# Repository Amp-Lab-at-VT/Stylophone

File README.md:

## Members
Jivitesh Kukreja, Electrical Engineering (2024)\
jiviteshkuk26@vt.edu

## Repo Link
<a class="button is-link" href="https://github.com/Amp-Lab-at-VT/Stylophone">Stylophone</a>

## Photo
/web/img/Stylophone/hero.png

## Mentor
Richard Gibbons

## Current Status
In Progress

## Project Overview
# About Stylophone
Stylophone is a musical instrument that contains 20 keys each associated with a distinct musical note. Every time the stylus touches a key frequency associated with that key is heard on the speaker. 
Stylophone can shfit the octace associated with a key, up or down with a flick of a switch. There is also vibrato mode which is basically modulating the frequency of each key to make it sound "alienish".
# About This Project
This Project aims to reverse engineering a stylophone using a modern TLC555 timer IC and a old Programable Unijunction Transistor. 
The resevred engineered version aims to included modern features like power using type C, low power consumtion while idle and under load, support for low impedance speaker, and rechargable battery. 
This project also serves to see which sounds better the digital version based on the 555 timer or the analog version based on PUT as the orginal stylophone.

## Educational Value Added
This Project with help me learn:
1. How to design low frequency oscillators
2. How to a simple audio amplifier 
3. How to design PCB

## Tasks
1. Design a square wave generator using TLC555 that produces different frequencies with different resistor values.
2. Design an audio amplifier that drives the speaker.
3. Design a low-frequency sine wave generator for vibrato effect.
4. Power everything with a USB C connector. 

[//]: #Design Decisions

[//]: ## Design Misc

[//]: ## Steps for Documenting Your Design Process

## Fabrication Files
<a class="button is-link" href="https://github.com/Amp-Lab-at-VT/Stylophone/blob/main/Fabrication%20Files/PUT/gerber_files_with_battery.zip">Gerber Files</a>
<a class="button is-link" href="https://github.com/Amp-Lab-at-VT/Stylophone/blob/main/Fabrication%20Files/PUT/Stylophone_with_battery.csv">Bill Of Materials</a>

## Timeline
SEPTEMBER: Circuit Design\
OCTOBER: PCB Design and Protoboard Testing\
NOVEMBER: Assembly and Testing\

## Useful Links
https://www.waitingforfriday.com/?p=334 \
https://www.instructables.com/Retro-Stylophone-NE555-Based/

[//]: ## Log

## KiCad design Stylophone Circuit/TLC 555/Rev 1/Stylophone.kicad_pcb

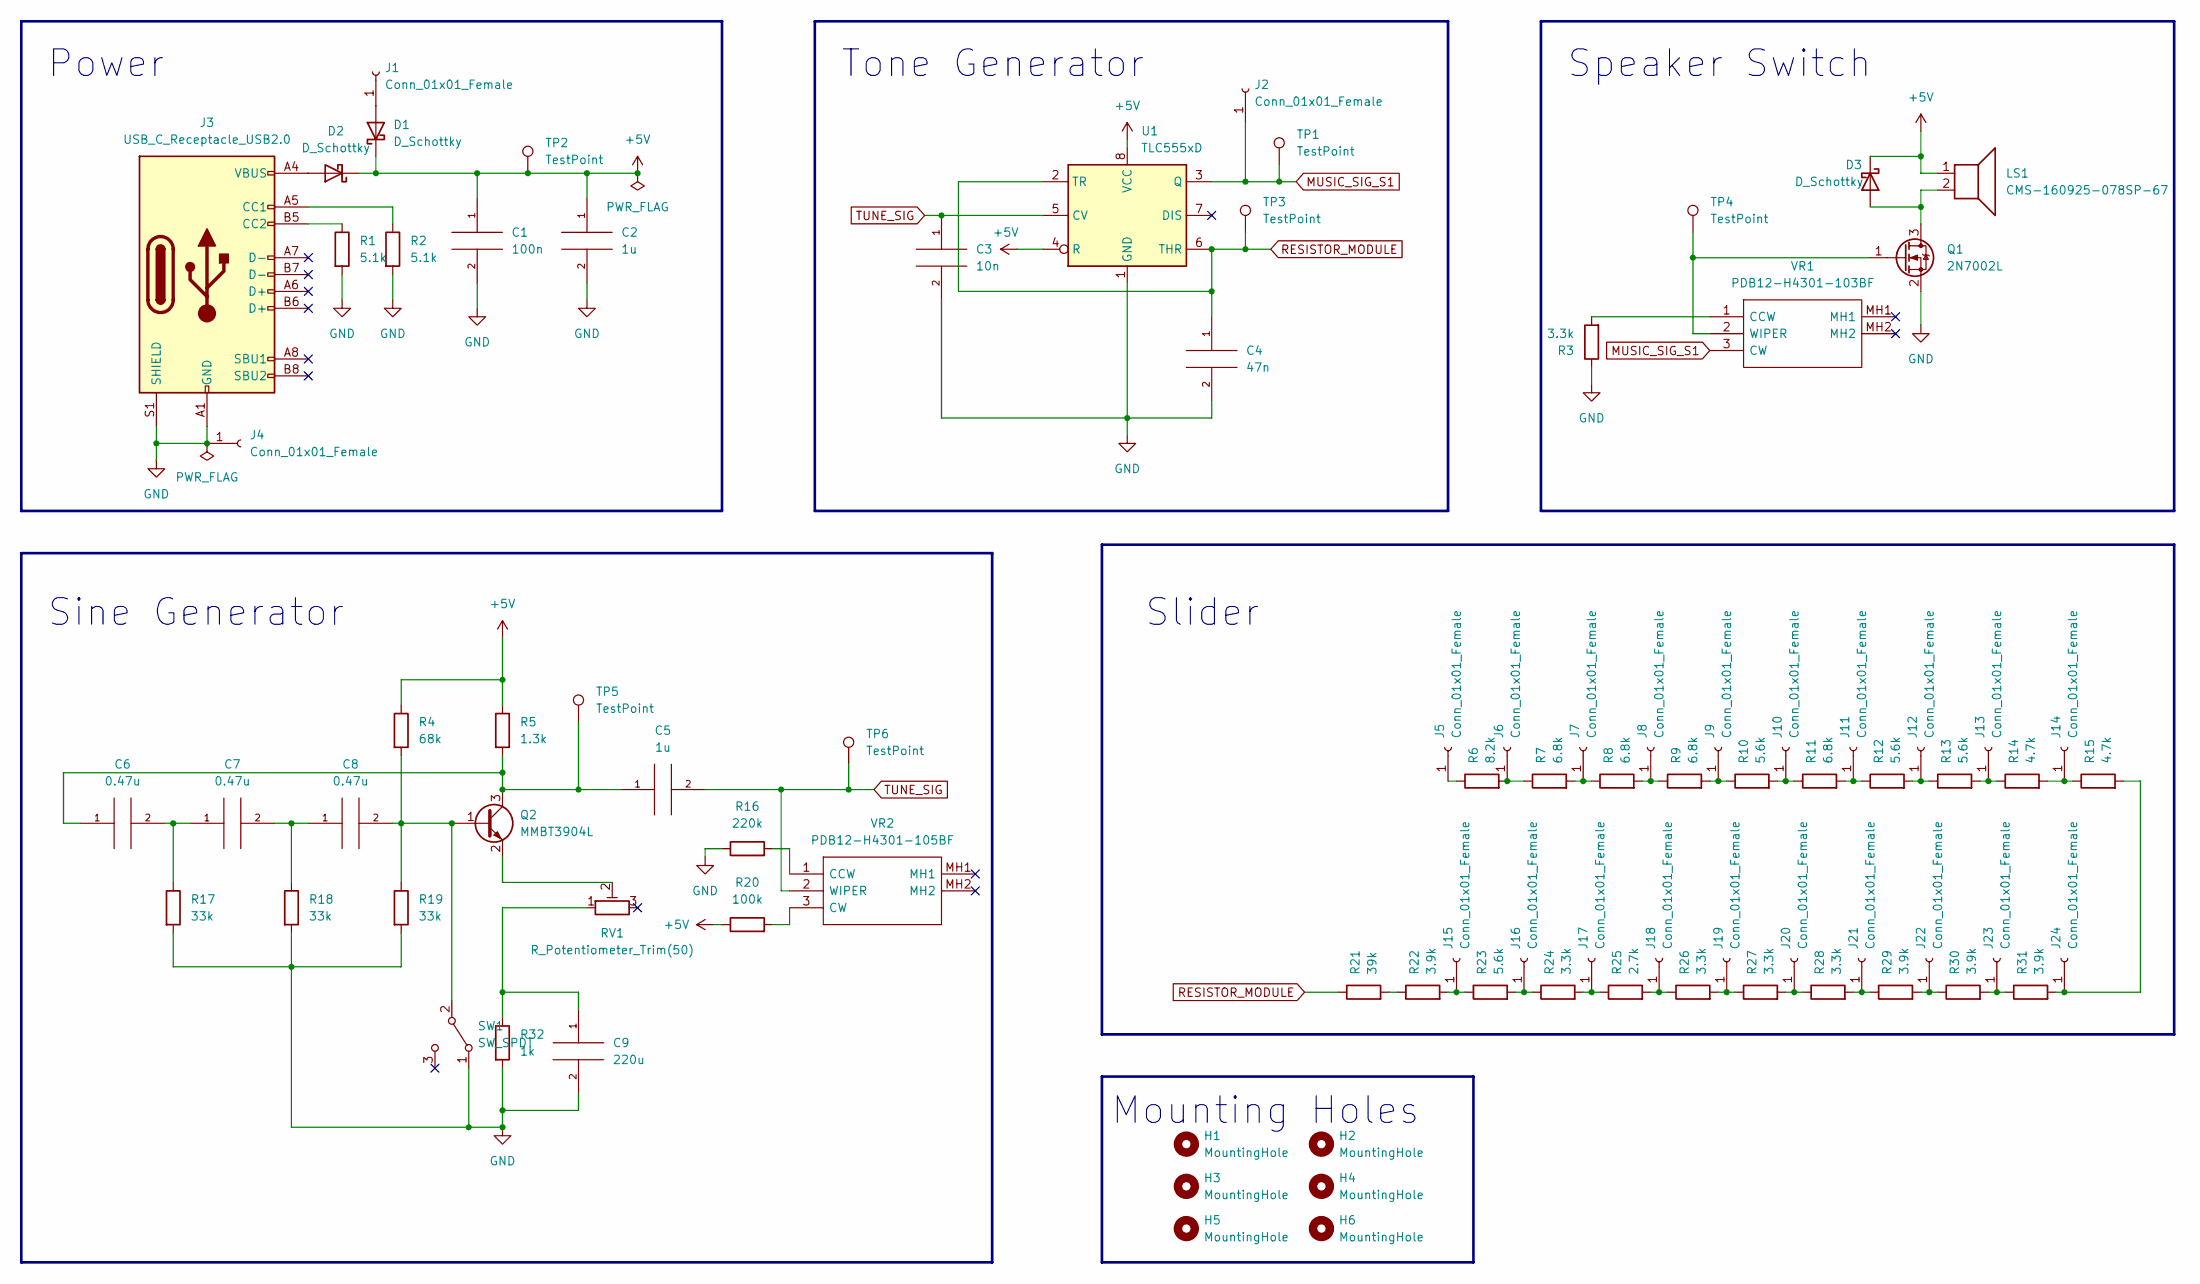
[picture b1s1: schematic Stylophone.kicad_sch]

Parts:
C1: 100n; C_0402_1005Metric
C2, C5: 1u; C_0603_1608Metric
C3: 10n; C_0201_0603Metric
C4: 47n; C_0402_1005Metric
C6, C7, C8: 0.47u; C_0603_1608Metric
C9: 220u; CP_Elec_6.3x7.7
D1, D2, D3: D_Schottky; D_SOD-123
H1, H2, H3, H4, H5, H6: MountingHole; MountingHole_2.7mm_M2.5
J1, J2, J4: Conn_01x01_Female; SolderWirePad_1x01_SMD_1x2mm
J3: USB_C_Receptacle_USB2.0; GCTUSB4125GFA190
J5, J8, J13, J19: Conn_01x01_Female; Note-Left
J6, J9, J11, J14, J16, J18, J21, J23: Conn_01x01_Female; Note-Sharp
J7, J12, J15, J20: Conn_01x01_Female; Note-Right
J10, J17, J22, J24: Conn_01x01_Female; Note-Center
LS1: CMS-160925-078SP-67; CMS160925078SP67
Q1: 2N7002L; SOT-23
Q2: MMBT3904L; SOT-23
R1, R2: 5.1k; R_0201_0603Metric
R3, R24, R26, R27, R28: 3.3k; R_0402_1005Metric
R4: 68k; R_0402_1005Metric
R5: 1.3k; R_0402_1005Metric
R6: 8.2k; R_0402_1005Metric
R7, R8, R9, R11: 6.8k; R_0402_1005Metric
R10, R12, R13, R23: 5.6k; R_0402_1005Metric
R14, R15: 4.7k; R_0402_1005Metric
R16: 220k; R_0402_1005Metric
R17, R18, R19: 33k; R_0402_1005Metric
R20: 100k; R_0402_1005Metric
R21: 39k; R_0402_1005Metric
R22, R29, R30, R31: 3.9k; R_0402_1005Metric
R25: 2.7k; R_0402_1005Metric
R32: 1k; R_0402_1005Metric
RV1: R_Potentiometer_Trim(50); Potentiometer_Bourns_3314J_Vertical
SW1: SW_SPDT; OS102011MA1QN1
TP1, TP2, TP3, TP4, TP5, TP6: TestPoint; TestPoint_Pad_D1.5mm
U1: TLC555xD; SOIC-8_3.9x4.9mm_P1.27mm
VR1: PDB12-H4301-103BF; PDB12H4301103BF; Mouser Part Number 652-PDB12-H4301103BF
VR2: PDB12-H4301-105BF; PDB12H4301105BF; Mouser Part Number 652-PDB12-H4301105BF

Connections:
+5V: C1.1, C2.1, D1.1 (K), D2.1 (K), D3.1 (K), LS1.1, R4.1, R5.1, R20.1, TP2.1, U1.4 (R), U1.8 (VCC)
GND: C1.2, C2.2, C3.2, C4.2, C9.2, J3.A1 (GND), J3.A12 (GND), J3.B1 (GND), J3.B12 (GND), J3.S1 (SHIELD), J4.1, Q1.2 (S), R1.2, R2.2, R3.1, R16.1, R17.2, R18.2, R19.2, R32.2, SW1.1 (A), U1.1 (GND)
MUSIC_SIG_S1: J2.1, TP1.1, U1.3 (Q), VR1.3 (CW)
unnamed: C5.1, C6.1, Q2.3 (C), R5.2, TP5.1
unnamed: C6.2, C7.1, R17.1
unnamed: C7.2, C8.1, R18.1
unnamed: C8.2, Q2.1 (B), R4.2, R19.1, SW1.2 (B)
unnamed: C9.1, R32.1, RV1.1
unnamed: D1.2 (A), J1.1
unnamed: D2.2 (A), J3.A4 (VBUS), J3.A9 (VBUS), J3.B4 (VBUS), J3.B9 (VBUS)
unnamed: D3.2 (A), LS1.2, Q1.3 (D)
unnamed: J3.A5 (CC1), R2.1
unnamed: J3.B5 (CC2), R1.1
unnamed: J5.1, R6.1
unnamed: J6.1, R6.2, R7.1
unnamed: J7.1, R7.2, R8.1
unnamed: J8.1, R8.2, R9.1
unnamed: J9.1, R9.2, R10.1
unnamed: J10.1, R10.2, R11.1
unnamed: J11.1, R11.2, R12.1
unnamed: J12.1, R12.2, R13.1
unnamed: J13.1, R13.2, R14.1
unnamed: J14.1, R14.2, R15.1
unnamed: J15.1, R22.2, R23.1
unnamed: J16.1, R23.2, R24.1
unnamed: J17.1, R24.2, R25.1
unnamed: J18.1, R25.2, R26.1
unnamed: J19.1, R26.2, R27.1
unnamed: J20.1, R27.2, R28.1
unnamed: J21.1, R28.2, R29.1
unnamed: J22.1, R29.2, R30.1
unnamed: J23.1, R30.2, R31.1
unnamed: J24.1, R15.2, R31.2
unnamed: Q1.1 (G), TP4.1, VR1.2 (WIPER)
unnamed: Q2.2 (E), RV1.2
unnamed: R3.2, VR1.1 (CCW)
unnamed: R16.2, VR2.1 (CCW)
unnamed: R20.2, VR2.3 (CW)
unnamed: R21.2, R22.1
RESISTOR_MODULE: C4.1, R21.1, TP3.1, U1.2 (TR), U1.6 (THR)
TUNE_SIG: C3.1, C5.2, TP6.1, U1.5 (CV), VR2.2 (WIPER)

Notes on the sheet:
Tone Generator
Mounting Holes
Power
Speaker Switch
Sine Generator
Slider

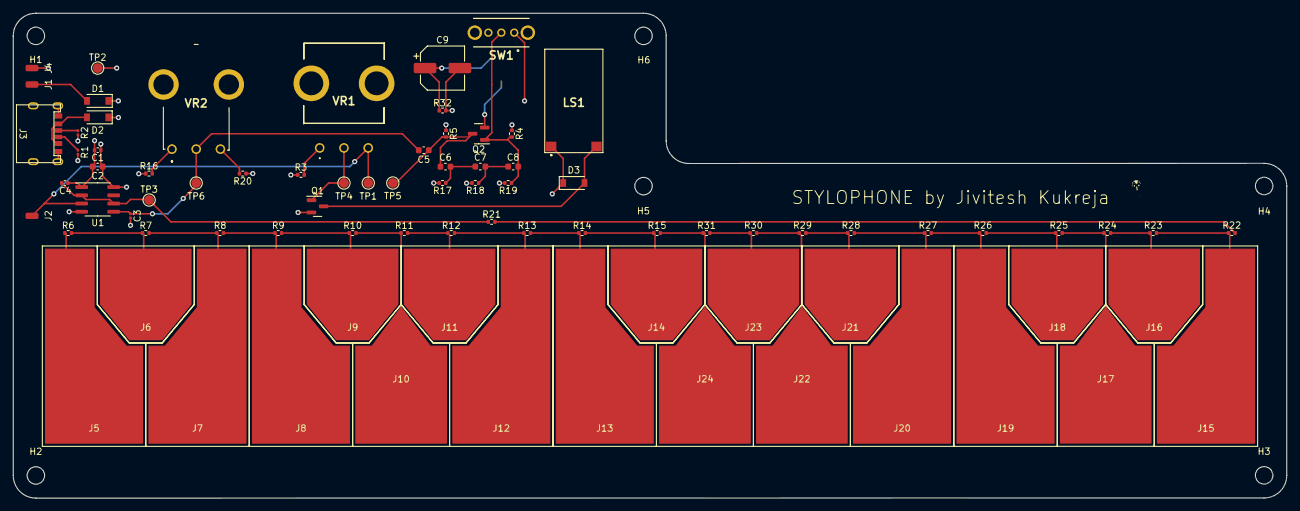
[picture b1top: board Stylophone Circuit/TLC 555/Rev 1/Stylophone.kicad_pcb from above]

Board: 4 copper layers, 197.0 x 75.0 mm, 88 parts (1 on the bottom side), 41 nets.

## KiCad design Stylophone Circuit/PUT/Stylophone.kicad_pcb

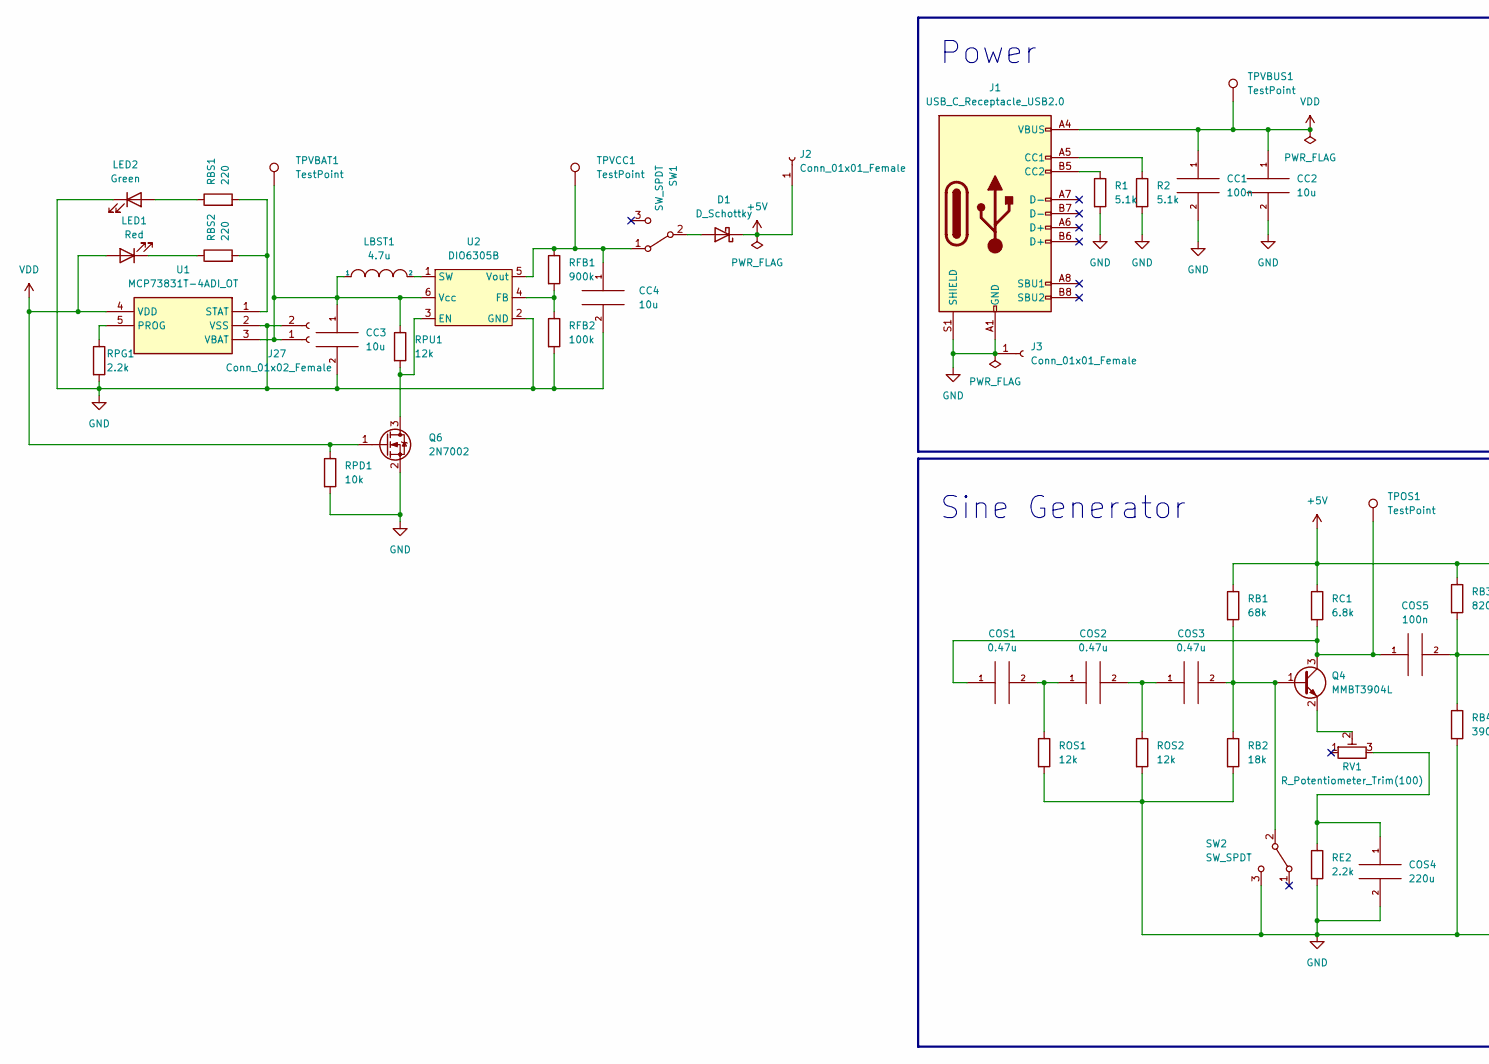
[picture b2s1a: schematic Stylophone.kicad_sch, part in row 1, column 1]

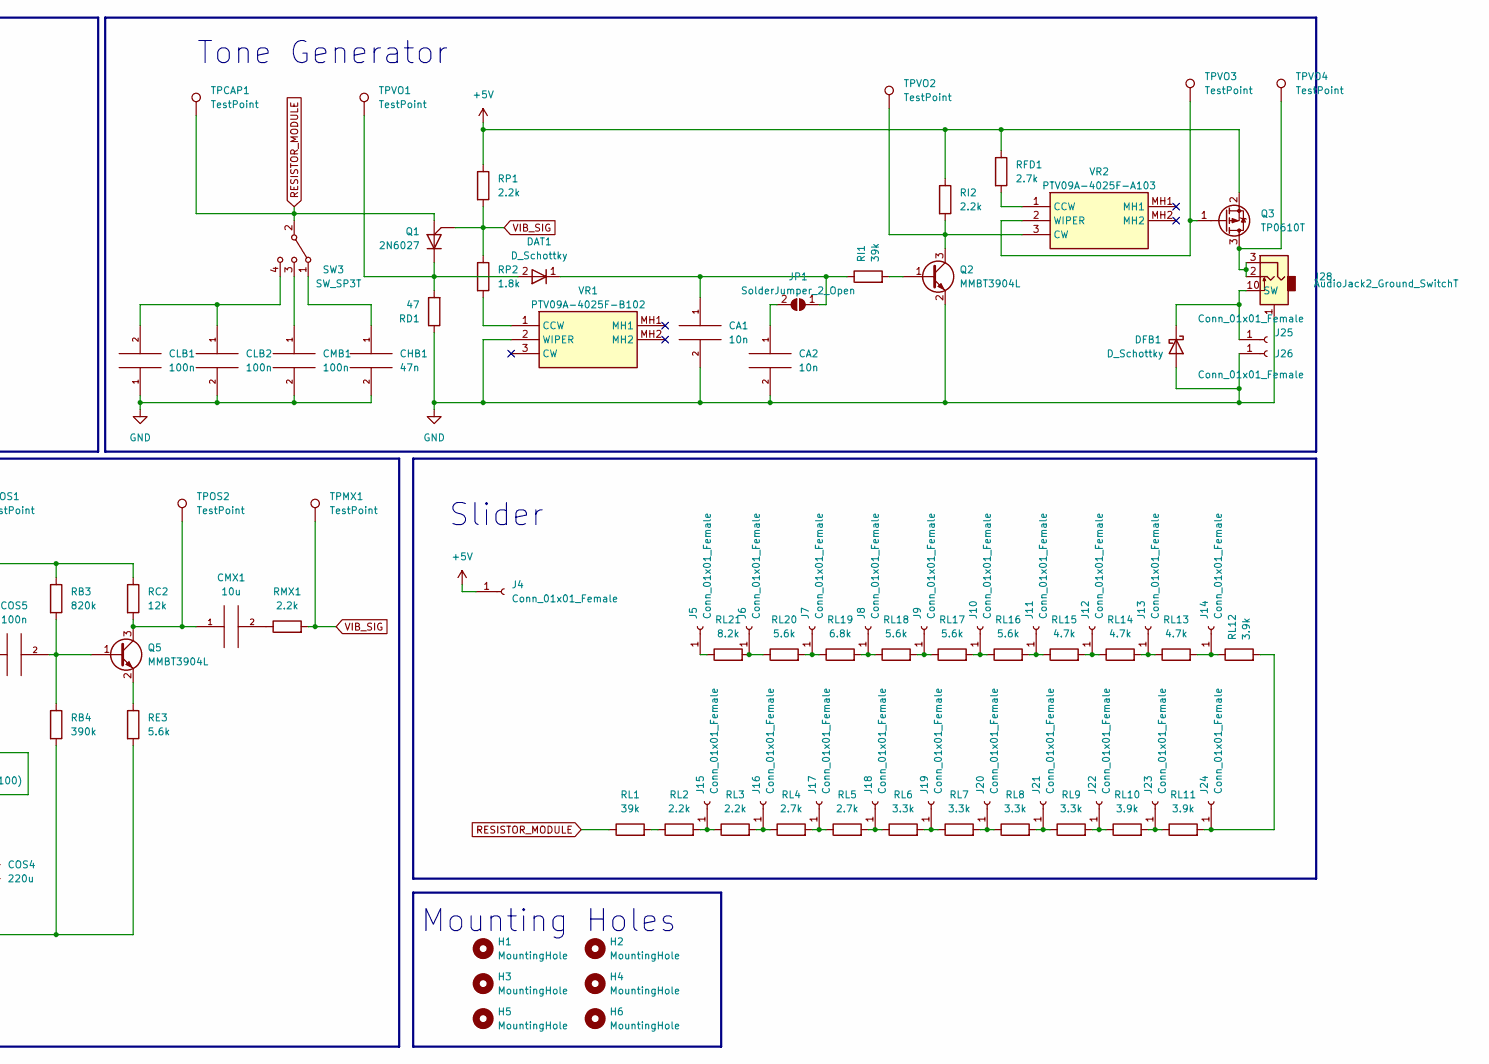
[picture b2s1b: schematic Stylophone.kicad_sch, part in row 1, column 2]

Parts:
CA1, CA2: 10n; C_0603_1608Metric_Pad1.08x0.95mm_HandSolder
CC1: 100n; C_0603_1608Metric_Pad1.08x0.95mm_HandSolder
CC2, CC3, CC4: 10u; C_1206_3216Metric_Pad1.33x1.80mm_HandSolder
CHB1: 47n; C_0603_1608Metric_Pad1.08x0.95mm_HandSolder
CLB1, CLB2: 100n; C_0603_1608Metric_Pad1.08x0.95mm_HandSolder
CMB1: 100n; C_0603_1608Metric_Pad1.08x0.95mm_HandSolder
CMX1: 10u; C_1206_3216Metric_Pad1.33x1.80mm_HandSolder
COS1, COS2, COS3: 0.47u; C_0805_2012Metric_Pad1.18x1.45mm_HandSolder
COS4: 220u; CP_Elec_6.3x7.7
COS5: 100n; C_0603_1608Metric_Pad1.08x0.95mm_HandSolder
D1: D_Schottky; D_SOD-123
DAT1: D_Schottky; D_SOD-123; Mouser Part Number 512-S1A
DFB1: D_Schottky; D_SOD-123
H1, H2, H3, H4, H5, H6: MountingHole; MountingHole_2.7mm_M2.5
J1: USB_C_Receptacle_USB2.0; GCTUSB4125GFA190
J2, J3, J4, J25, J26: Conn_01x01_Female; SolderWirePad_1x01_SMD_1x2mm
J5, J8, J13, J19: Conn_01x01_Female; Note-Left
J6, J9, J11, J14, J16, J18, J21, J23: Conn_01x01_Female; Note-Sharp
J7, J12, J15, J20: Conn_01x01_Female; Note-Right
J10, J17, J22, J24: Conn_01x01_Female; Note-Center
J27: Conn_01x02_Female; JST_PH_S2B-PH-K_1x02_P2.00mm_Horizontal
J28: AudioJack2_Ground_SwitchT; SJ23593BSMTTR
JP1: SolderJumper_2_Open; SolderJumper-2_P1.3mm_Open_TrianglePad1.0x1.5mm
LBST1: 4.7u; 74408053004_5030
LED1: Red; LED_0603_1608Metric_Pad1.05x0.95mm_HandSolder
LED2: Green; LED_0603_1608Metric_Pad1.05x0.95mm_HandSolder
Q1: 2N6027; TO-92_Inline_Horizontal2
Q2, Q4, Q5: MMBT3904L; SOT-23
Q3: TP0610T; SOT-23
Q6: 2N7002; SOT-23
R1, R2: 5.1k; R_0805_2012Metric_Pad1.20x1.40mm_HandSolder
RB1: 68k; R_0805_2012Metric_Pad1.20x1.40mm_HandSolder
RB2: 18k; R_0805_2012Metric_Pad1.20x1.40mm_HandSolder
RB3: 820k; R_0805_2012Metric_Pad1.20x1.40mm_HandSolder
RB4: 390k; R_0805_2012Metric_Pad1.20x1.40mm_HandSolder
RBS1, RBS2: 220; R_0805_2012Metric_Pad1.20x1.40mm_HandSolder
RC1: 6.8k; R_0805_2012Metric_Pad1.20x1.40mm_HandSolder
RC2: 12k; R_0805_2012Metric_Pad1.20x1.40mm_HandSolder
RD1: 47; R_0805_2012Metric_Pad1.20x1.40mm_HandSolder
RE2: 2.2k; R_0805_2012Metric_Pad1.20x1.40mm_HandSolder
RE3: 5.6k; R_0805_2012Metric_Pad1.20x1.40mm_HandSolder
RFB1: 900k; R_0805_2012Metric_Pad1.20x1.40mm_HandSolder
RFB2: 100k; R_0805_2012Metric_Pad1.20x1.40mm_HandSolder
RFD1: 2.7k; R_0805_2012Metric_Pad1.20x1.40mm_HandSolder
RI1: 39k; R_0805_2012Metric_Pad1.20x1.40mm_HandSolder
RI2: 2.2k; R_0805_2012Metric_Pad1.20x1.40mm_HandSolder
RL1: 39k; R_0805_2012Metric_Pad1.20x1.40mm_HandSolder
RL2, RL3: 2.2k; R_0805_2012Metric_Pad1.20x1.40mm_HandSolder
RL4, RL5: 2.7k; R_0805_2012Metric_Pad1.20x1.40mm_HandSolder
RL6, RL7, RL8, RL9: 3.3k; R_0805_2012Metric_Pad1.20x1.40mm_HandSolder
RL10, RL11, RL12: 3.9k; R_0805_2012Metric_Pad1.20x1.40mm_HandSolder
RL13, RL14, RL15: 4.7k; R_0805_2012Metric_Pad1.20x1.40mm_HandSolder
RL16, RL17, RL18, RL20: 5.6k; R_0805_2012Metric_Pad1.20x1.40mm_HandSolder
RL19: 6.8k; R_0805_2012Metric_Pad1.20x1.40mm_HandSolder
RL21: 8.2k; R_0805_2012Metric_Pad1.20x1.40mm_HandSolder
RMX1: 2.2k; R_0805_2012Metric_Pad1.20x1.40mm_HandSolder
ROS1, ROS2: 12k; R_0805_2012Metric_Pad1.20x1.40mm_HandSolder
RP1: 2.2k; R_0805_2012Metric_Pad1.20x1.40mm_HandSolder
RP2: 1.8k; R_0805_2012Metric_Pad1.20x1.40mm_HandSolder
RPD1: 10k; R_0805_2012Metric_Pad1.20x1.40mm_HandSolder
RPG1: 2.2k; R_0805_2012Metric_Pad1.20x1.40mm_HandSolder
RPU1: 12k; R_0805_2012Metric_Pad1.20x1.40mm_HandSolder
RV1: R_Potentiometer_Trim(100); TC33X2503E
SW1, SW2: SW_SPDT; OS102011MA1QN1
SW3: SW_SP3T; OS103011MA7QP1
TPCAP1: TestPoint; TestPoint_Pad_D1.5mm
TPMX1: TestPoint; TestPoint_Pad_D1.5mm
TPOS1, TPOS2: TestPoint; TestPoint_Pad_D1.5mm
TPVBAT1: TestPoint; TestPoint_Pad_D1.5mm
TPVBUS1: TestPoint; TestPoint_Pad_D1.5mm
TPVCC1: TestPoint; TestPoint_Pad_D1.5mm
TPVO1, TPVO2, TPVO3, TPVO4: TestPoint; TestPoint_Pad_D1.5mm
U1: MCP73831T-4ADI_OT; TSOT-23-5_HandSoldering; Mouser Part Number 579-MCP73831T4ADIOT
U2: DIO6305B; TSOT-23-6_HandSoldering
VR1: PTV09A-4025F-B102; PTV09A4025FB102; Mouser Part Number 652-PTV09A-4025FB102
VR2: PTV09A-4025F-A103; PTV09A4025FA103; Mouser Part Number 652-PTV09A4025FA103

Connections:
+5V: D1.1 (K), J2.1, J4.1, Q3.2 (S), RB1.1, RB3.1, RC1.1, RC2.1, RFD1.1, RI2.1, RP1.1
GND: CA1.2, CA2.2, CC1.2, CC2.2, CC3.2, CC4.2, CHB1.2, CLB1.1, CLB2.2, CMB1.2, COS4.2, DFB1.2 (A), J1.A1 (GND), J1.A12 (GND), J1.B1 (GND), J1.B12 (GND), J1.S1 (SHIELD), J3.1, J26.1, J27.2, J28.1, LED2.1 (K), Q2.2 (E), Q6.2 (S), R1.2, R2.2, RB2.2, RB4.2, RD1.1, RE2.2, RE3.2, RFB2.2, ROS1.2, ROS2.2, RPD1.2, RPG1.2, SW2.3 (C), U1.2 (VSS), U2.2 (GND), VR1.2 (WIPER)
unnamed: CA1.1, DAT1.1 (K), JP1.1 (A), RI1.1
unnamed: CA2.1, JP1.2 (B)
unnamed: CC3.1, J27.1, LBST1.1, RPU1.1, TPVBAT1.1, U1.3 (VBAT), U2.6 (Vcc)
unnamed: CC4.1, RFB1.1, SW1.1 (A), TPVCC1.1, U2.5 (Vout)
unnamed: CHB1.1, SW3.1
unnamed: CLB1.2, CLB2.1, SW3.4
unnamed: CMB1.1, SW3.3
unnamed: CMX1.1, Q5.3 (C), RC2.2, TPOS2.1
unnamed: CMX1.2, RMX1.1
unnamed: COS1.1, COS5.1, Q4.3 (C), RC1.2, TPOS1.1
unnamed: COS1.2, COS2.1, ROS1.1
unnamed: COS2.2, COS3.1, ROS2.1
unnamed: COS3.2, Q4.1 (B), RB1.2, RB2.1, SW2.2 (B)
unnamed: COS4.1, RE2.1, RV1.3
unnamed: COS5.2, Q5.1 (B), RB3.2, RB4.1
unnamed: D1.2 (A), SW1.2 (B)
unnamed: DAT1.2 (A), Q1.3 (Cathode), RD1.2, TPVO1.1
unnamed: DFB1.1 (K), J25.1, J28.10 (SW)
unnamed: J1.A5 (CC1), R2.1
unnamed: J1.B5 (CC2), R1.1
unnamed: J5.1, RL21.1
unnamed: J6.1, RL20.1, RL21.2
unnamed: J7.1, RL19.1, RL20.2
unnamed: J8.1, RL18.1, RL19.2
unnamed: J9.1, RL17.1, RL18.2
unnamed: J10.1, RL16.1, RL17.2
unnamed: J11.1, RL15.1, RL16.2
unnamed: J12.1, RL14.1, RL15.2
unnamed: J13.1, RL13.1, RL14.2
unnamed: J14.1, RL12.1, RL13.2
unnamed: J15.1, RL2.2, RL3.1
unnamed: J16.1, RL3.2, RL4.1
unnamed: J17.1, RL4.2, RL5.1
unnamed: J18.1, RL5.2, RL6.1
unnamed: J19.1, RL6.2, RL7.1
unnamed: J20.1, RL7.2, RL8.1
unnamed: J21.1, RL8.2, RL9.1
unnamed: J22.1, RL9.2, RL10.1
unnamed: J23.1, RL10.2, RL11.1
unnamed: J24.1, RL11.2, RL12.2
unnamed: J28.2, J28.3, Q3.3 (D), TPVO4.1
unnamed: LBST1.2, U2.1 (SW)
unnamed: LED1.1 (K), RBS2.1
unnamed: LED2.2 (A), RBS1.1
unnamed: Q2.1 (B), RI1.2
unnamed: Q2.3 (C), RI2.2, TPVO2.1, VR2.3 (CW)
unnamed: Q3.1 (G), TPVO3.1, VR2.2 (WIPER)
unnamed: Q4.2 (E), RV1.2
unnamed: Q5.2 (E), RE3.1
unnamed: Q6.3 (D), RPU1.2, U2.3 (EN)
unnamed: RBS1.2, RBS2.2, U1.1 (STAT)
unnamed: RFB1.2, RFB2.1, U2.4 (FB)
unnamed: RFD1.2, VR2.1 (CCW)
unnamed: RL1.2, RL2.1
unnamed: RP2.2, VR1.1 (CCW)
unnamed: RPG1.1, U1.5 (PROG)
RESISTOR_MODULE: Q1.1 (Anode), RL1.1, SW3.2, TPCAP1.1
VDD: CC1.1, CC2.1, J1.A4 (VBUS), J1.A9 (VBUS), J1.B4 (VBUS), J1.B9 (VBUS), LED1.2 (A), Q6.1 (G), RPD1.1, TPVBUS1.1, U1.4 (VDD)
VIB_SIG: Q1.2 (Gate), RMX1.2, RP1.2, RP2.1, TPMX1.1

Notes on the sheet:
Tone Generator
Mounting Holes
Power
Sine Generator
Slider

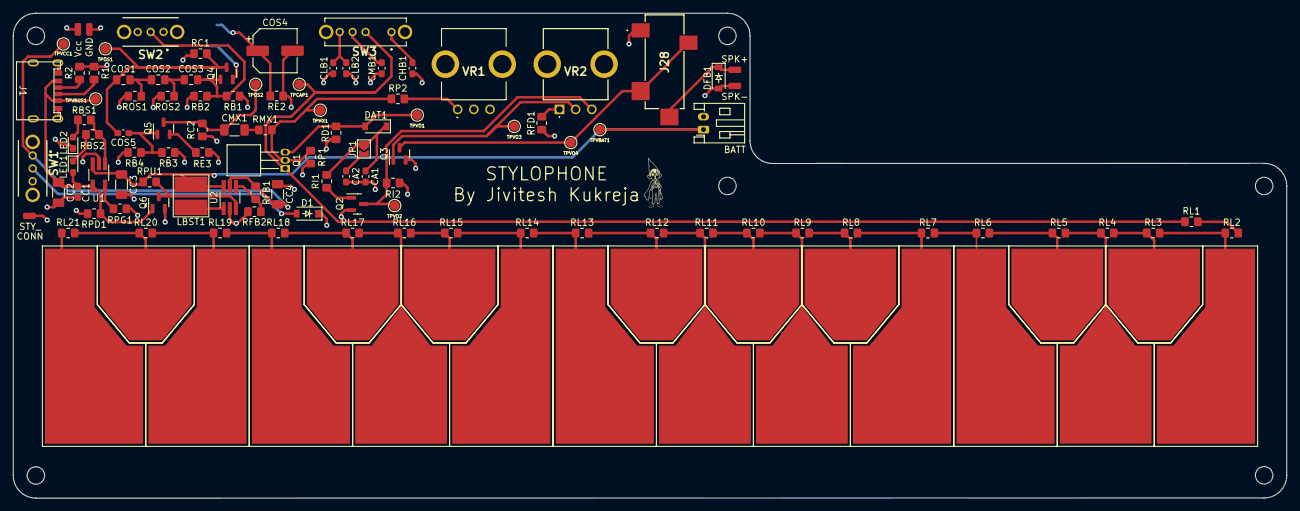
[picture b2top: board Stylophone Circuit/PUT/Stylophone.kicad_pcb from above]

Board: 4 copper layers, 197.0 x 75.0 mm, 130 parts (1 on the bottom side), 61 nets.

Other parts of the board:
G1: LOGO

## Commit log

2022-10-04 Added Project Description files and image
2022-10-04 Fixed Images
2022-10-04 Fixed Table
2022-11-09 Added fabrication files and bom
2022-11-09 Updated the project
2022-11-17 Updated BOM and page
2023-01-27 Updates for new website
2023-07-31 added analog version
2023-07-31 fixed bom for analog version
